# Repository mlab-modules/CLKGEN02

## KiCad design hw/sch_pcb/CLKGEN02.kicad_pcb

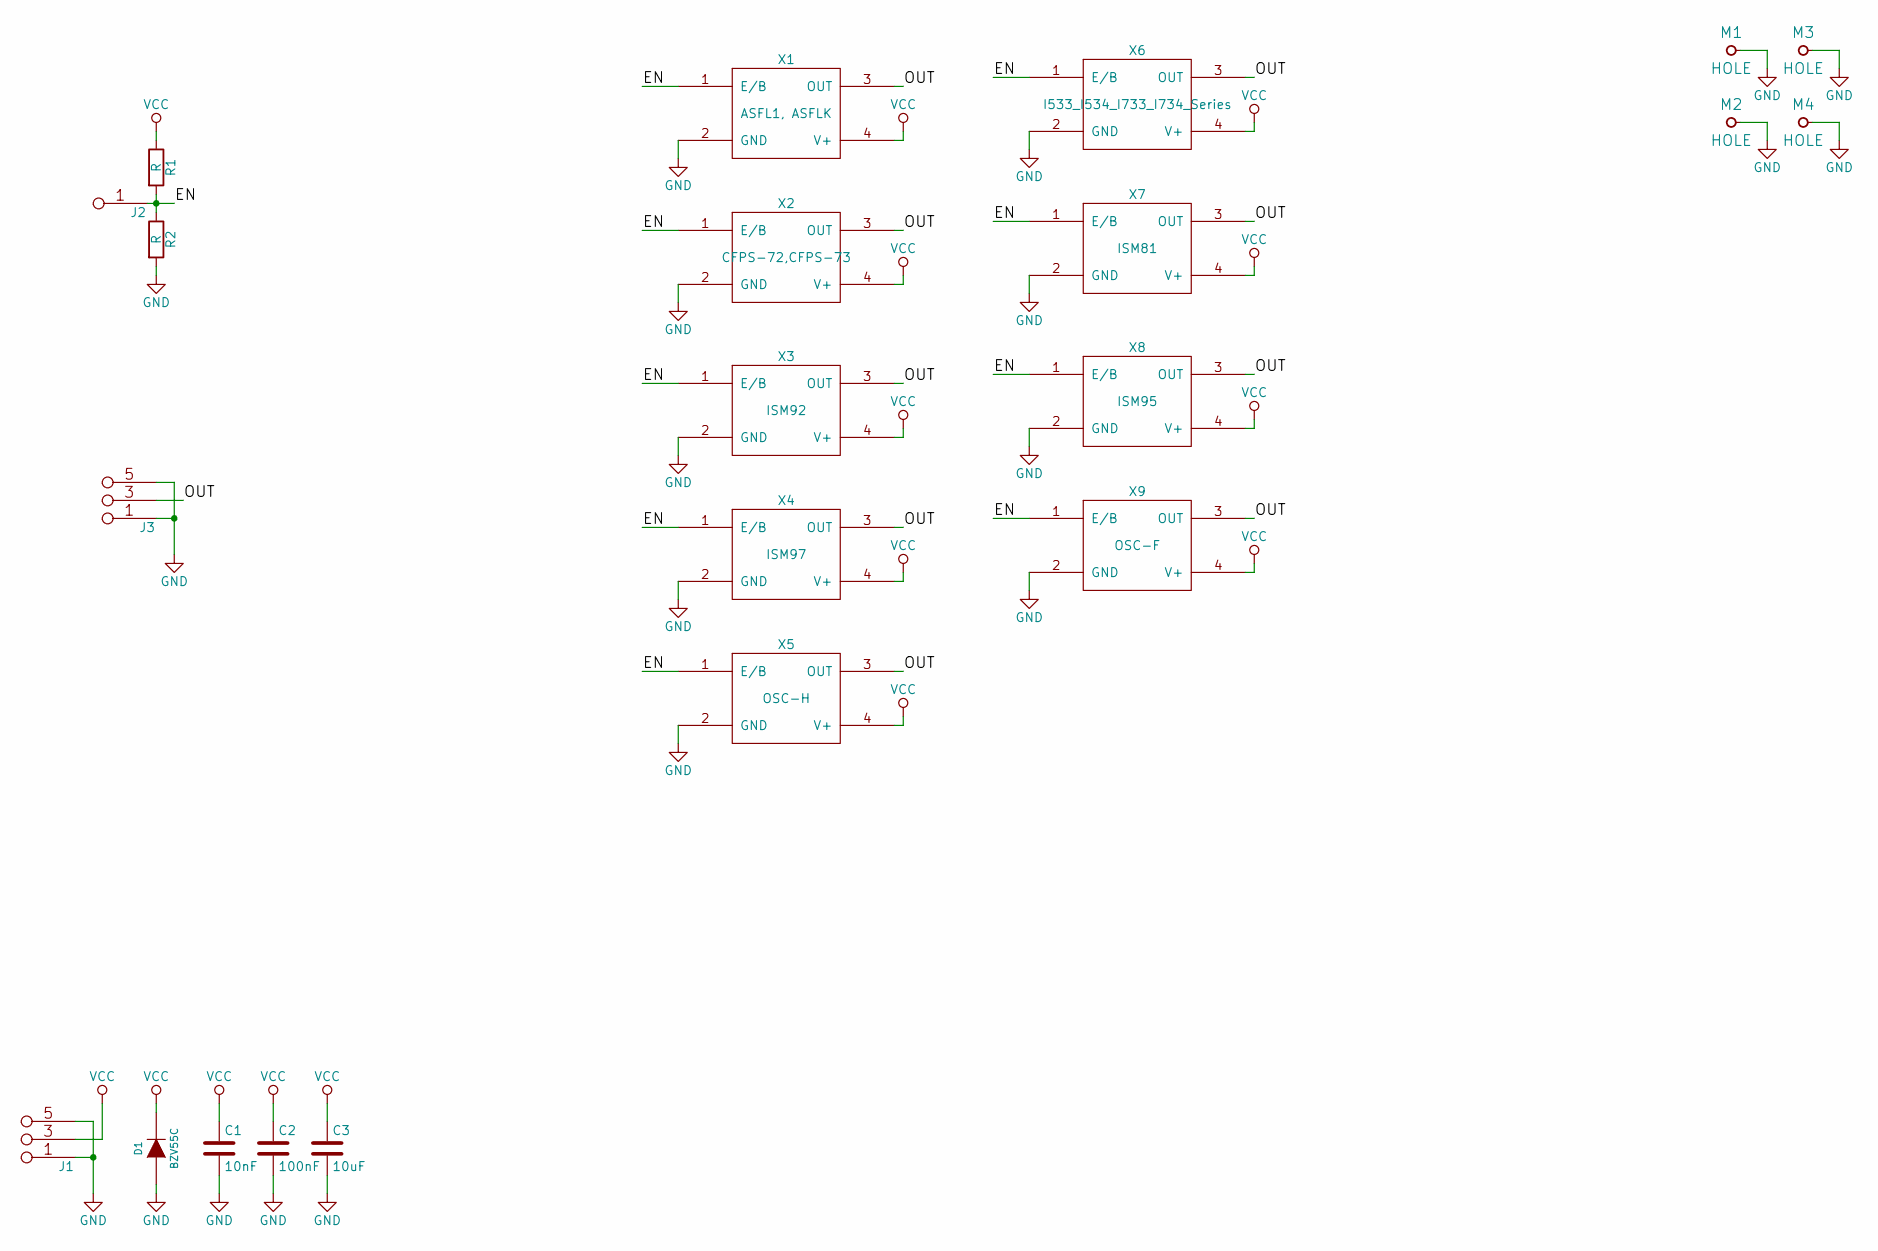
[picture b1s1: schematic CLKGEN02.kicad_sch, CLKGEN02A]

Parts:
C1: 10nF; SMD-0805
C2: 100nF; SMD-0805
C3: 10uF; SMD-0805
D1: BZV55C; Diode-MiniMELF_Standard
J1, J3: JUMP_3X2; Straight_2x03
J2: JUMP_2x1; Straight_1x02
M1, M2, M3, M4: HOLE; MountingHole_3mm
R1, R2: R; SMD-0805
X1: ASFL1, ASFLK; ASFL1
X2: CFPS-72,CFPS-73; CFPS-72,73
X3: ISM92
X4: ISM97
X5: OSC-H
X6: I533_I534_I733_I734_Series; I533_1534_1733_1734
X7: ISM81
X8: ISM95
X9: OSC-F

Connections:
/EN: J2.1, J2.2, R1.2, R2.1, X1.1 (E/B), X2.1 (E/B), X3.1 (E/B), X4.1 (E/B), X5.1 (E/B), X6.1 (E/B), X7.1 (E/B), X8.1 (E/B), X9.1 (E/B)
/OUT: J3.3 (4), J3.4, X1.3 (OUT), X2.3 (OUT), X3.3 (OUT), X4.3 (OUT), X5.3 (OUT), X6.3 (OUT), X7.3 (OUT), X8.3 (OUT), X9.3 (OUT)
GND: C1.2, C2.2, C3.2, D1.2 (A), J1.1 (2), J1.2, J1.5 (6), J1.6, J3.1 (2), J3.2, J3.5 (6), J3.6, M1.1, M2.1, M3.1, M4.1, R2.2, X1.2 (GND), X2.2 (GND), X3.2 (GND), X4.2 (GND), X5.2 (GND), X6.2 (GND), X7.2 (GND), X8.2 (GND), X9.2 (GND)
VCC: C1.1, C2.1, C3.1, D1.1 (K), J1.3 (4), J1.4, R1.1, X1.4 (V+), X2.4 (V+), X3.4 (V+), X4.4 (V+), X5.4 (V+), X6.4 (V+), X7.4 (V+), X8.4 (V+), X9.4 (V+)

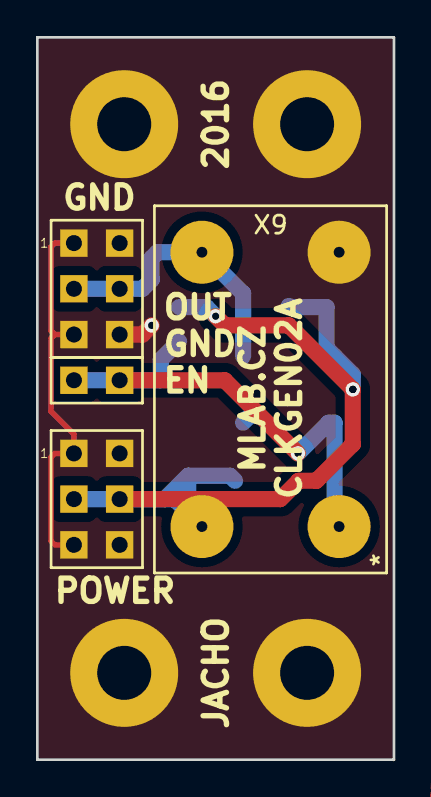
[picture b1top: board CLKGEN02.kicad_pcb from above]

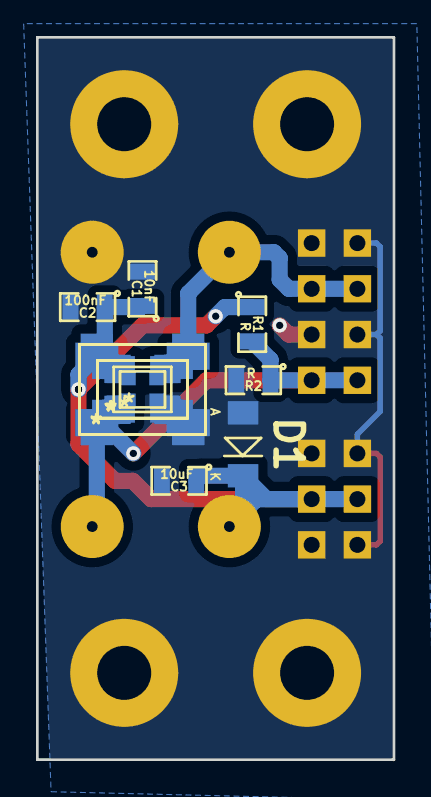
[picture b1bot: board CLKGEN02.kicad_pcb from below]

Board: 2 copper layers, 19.8 x 40.1 mm, 21 parts (13 on the bottom side), 4 nets.

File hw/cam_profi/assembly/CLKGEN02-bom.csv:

Component,Description,Part,References,Value,Footprint,Quantity Per PCB,Datasheet
1,,C,C1,10nF,SMD-0805,1,
2,,C,C2,100nF,SMD-0805,1,
3,,C,C3,10uF,SMD-0805,1,
4,,DIODE,D1,BZV55C,Diode-MiniMELF_Standard,1,
5,,JUMP_2x1,J2,JUMP_2x1,Straight_1x02,1,
6,,JUMP_3X2,J1J3,JUMP_3X2,Straight_2x03,2,
7,,R,R1R2,R,SMD-0805,2,
8,,IQXO/7X,X1,"ASFL1, ASFLK",ASFL1,1,
9,,IQXO/7X,X2,"CFPS-72,CFPS-73","CFPS-72,73",1,
10,,IQXO/7X,X6,I533_I534_I733_I734_Series,I533_1534_1733_1734,1,
11,,IQXO/7X,X7,ISM81,ISM81,1,
12,,IQXO/7X,X3,ISM92,ISM92,1,
13,,IQXO/7X,X8,ISM95,ISM95,1,
14,,IQXO/7X,X4,ISM97,ISM97,1,
15,,IQXO/7X,X9,OSC-F,OSC-F,1,
16,,IQXO/7X,X5,OSC-H,OSC-H,1,

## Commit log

2023-04-01 Adding force option to enable splitting in not fresh copy of Modules repository.
2023-07-20 update assets
2023-07-20 Update metadata files
2023-07-20 Update workflow files
2023-09-16 Update status
2023-09-17 Convert project to new KiCAD7.
2023-09-17 Update actions products
2023-09-17 Update metadata.yaml
    Select title image.
